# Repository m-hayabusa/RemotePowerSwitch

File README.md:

# M5Stamp C3 を PC のフロントパネルヘッダに繋いで、電源を Wi-Fi 越しに操作するやつ

## 必要なもの

-   基板
-   1 x M5Stamp C3 Mate あるいは M5Stamp C3U Mate
    -   Mate のセットでなく単体の場合は、適当なロープロファイルピンヘッダとピンソケットも用意してください
-   5 x 1608 チップ抵抗 / 100Ω 程度
-   3 x SOT-23 Nch MOSFET / BSS138 など
-   1 x SOD-123 定電流ダイオード or 定電流レギュレータ / 20mA 程度 NSI45020AT1G など
-   1 x L 字ピンヘッダー / 2.54 mm ピッチ 1 列 5 ピン
-   1 x L 字ピンソケット / 2.54 mm ピッチ 2 列 5 ピン

## つくりかた

-   下: GND ベタがないほう
-   表面: 表面実装部品のパターンがある面
-   裏面: LED+/LED-/PWR#/GND/NC の印字がある面

1. 表面に、定電流ダイオードと MOSFET をはんだづけする
2. 表面に、抵抗をはんだづけする。下から 5 つ
3. 裏面に、1x5 のピンヘッダをはんだづけする。LED+/LED-/PWR#/GND/NC の印字が見える方向
4. M5Stamp C3 に付属のピンヘッダを、M5Stamp にはんだづけする
5. 表面に、M5Stamp C3 に付属のピンソケットをはんだづけする。
   あるいは、M5Stamp につけたピンヘッダを直接基板にはんだづけしてもよい
6. 表面に、2x5 のピンソケットをはんだづけする。
   シルクで印がしてあるピンはマザーボード側で欠けてあるピンなので、可能ならソケットからピンを抜いて UV レジンか何かで埋めておくとよい
7. M5Stamp にファームウェアを書きこむ

## ファームウェアの書き込み; 初回

1. VisualStudio Code にプラグイン PlatformIO を追加
2. https://github.com/m-hayabusa/RemotePowerSwitch.git を clone する
3. PlatformIO で 2. のディレクトリを開く。VSCode の左側のバー、なんか触覚が生えてる顔のアイコンから
4. 下のバーの「Default (RemotePowerSwitch)」の部分をクリック、M5Stamp-C3 か M5Stamp-C3U かを選択
5. 下のバーの「→」をクリック、Upload
6. 適当なシリアルモニターで M5Stamp のポートを開く。PlatformIO なら画面下のバーのプラグのアイコンから。挙動が怪しいような気がするので Arduino IDE のシリアルモニタがおすすめ
7. シリアルモニターでこれらを送って設定:

```
WIFI.SSID:(2.4GHz な Wi-Fi ネットワークの SSID)
WIFI.PASSWORD:(Wi-Fi ネットワークのパスワード)
WEB.HOSTNAME:(mDNS で宣伝するホスト名)
WEB.PASSWORD:(Webページから操作するときに必要なパスワード, 設定しなければパスワードなしで操作できます / 解除する場合は空の文字列を設定)
```

8. "http://" + WEB.HOSTNAME + ".local"で接続できるはずです

## ファームウェアの更新

1. PlatformIO でファームウェアをビルド (下のバーの「✔️」)
2. "http://" + WEB.HOSTNAME + ".local/update" をブラウザで開く
3. Firmware.bin のボタンをクリック、プロジェクトのディレクトリ/.pio/M5Stamp-C3/firmware.bin を選択
4. Upload をクリック
5. アップロード・書き込みが終わると自動で再起動します

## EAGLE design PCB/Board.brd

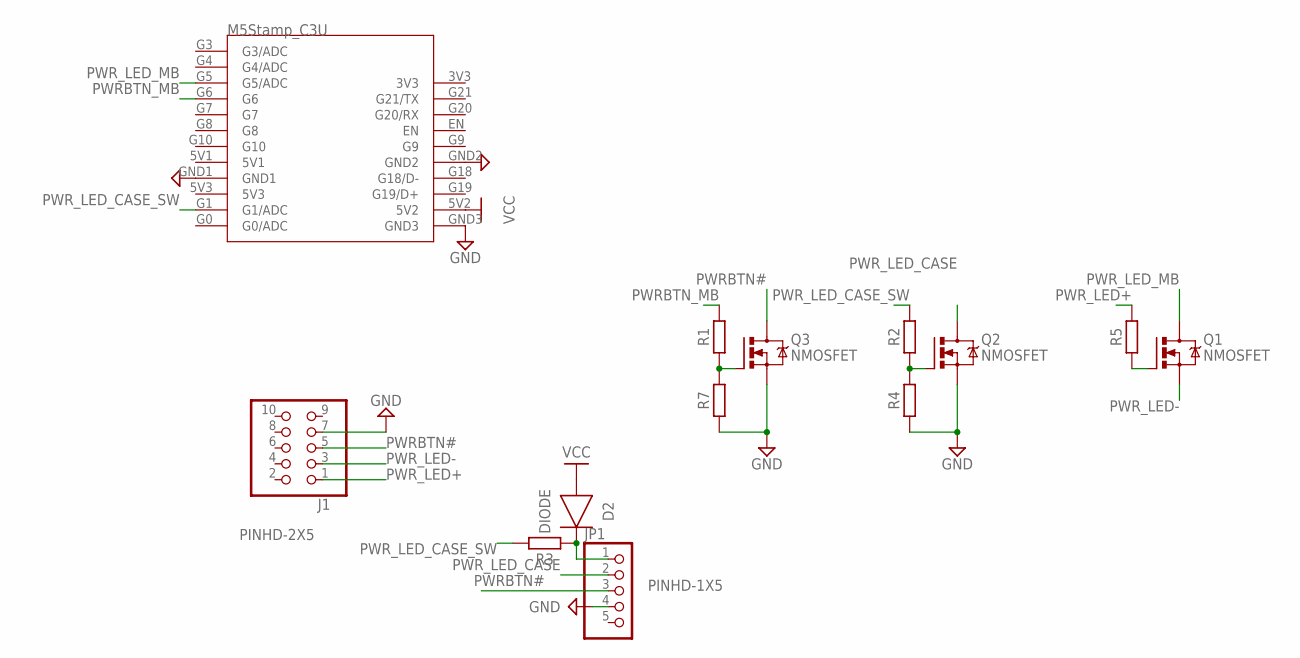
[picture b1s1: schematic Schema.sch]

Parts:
D2: DIODE; SODFL3718X115
J1: PINHD-2X5; 2X05
JP1: PINHD-1X5; 1X05
Q1, Q2, Q3: NMOSFET; SOT23
R1, R2, R3, R4, R5, R7: R_CHIP-0603(1608-METRIC); RESC1608X60
U$1: M5STAMP_C3UHEADER; M5STAMP_C3U_HEADER

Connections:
GND: J1.7, JP1.4, Q2.2 (S), Q3.2 (S), R4.1, R7.1, U$1.GND1, U$1.GND2, U$1.GND3
unnamed: Q3.1 (G), R1.1, R7.2
unnamed: Q2.1 (G), R2.1, R4.2
unnamed: D2.1 (C), JP1.1, R3.1
unnamed: Q1.1 (G), R5.1
PWRBTN#: J1.5, JP1.3, Q3.3 (D)
PWRBTN_MB: R1.2, U$1.G6
PWR_LED+: J1.1, R5.2
PWR_LED-: J1.3, Q1.2 (S)
PWR_LED_CASE: JP1.2, Q2.3 (D)
PWR_LED_CASE_SW: R2.2, R3.2, U$1.G1 (G1/ADC)
PWR_LED_MB: Q1.3 (D), U$1.G5 (G5/ADC)
VCC: D2.2 (A), U$1.5V2

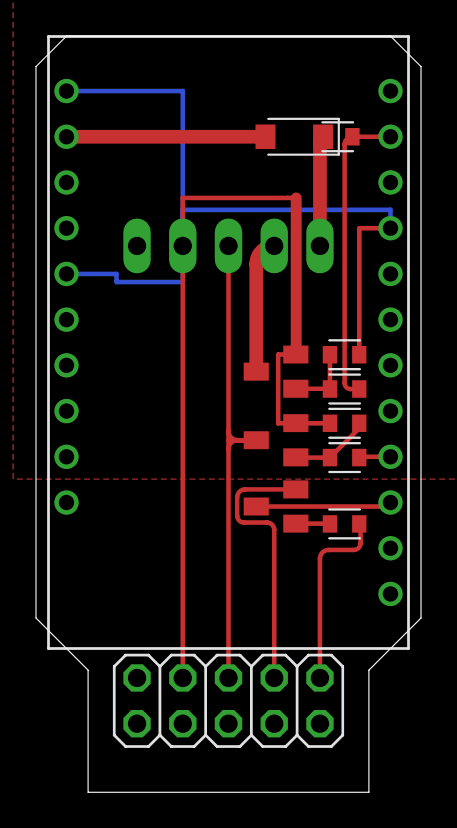
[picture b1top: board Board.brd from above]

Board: 2 copper layers, 21.4 x 42.0 mm, 13 parts (1 on the bottom side), 13 nets.

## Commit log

2023-01-10 Create LICENSE
2023-01-12 C3UでUSBシリアルを使うときの設定
2023-01-12 HTMLファイルの挿入方法を変更
2023-01-12 OTAアップデートできるように
2023-01-12 トップページをいい感じに
2023-01-12 初期化処理をsetupからそれぞれのタスクに移動
2023-01-12 トップページを携帯で見たときいい感じに
2023-01-13 グローバルな変数を減らす
2023-01-17 pinModeの設定ミス
2023-03-30 staticである意味がなかったので外した
2023-03-30 シリアルの受信バッファに何もないとき、待機せずループしていたのを修正
2023-03-30 光り方の違いがそこまでないのでsinを通すのをやめた
2023-03-30 シリアル通信の速度を変更
2023-03-31 パスを相対で指定するように変更
2023-03-31 見た目の調整
2023-03-31 シリアルの読み込み待機を減らした
2023-03-31 タスクの割り当てを変更
2023-04-01 フォーマッタの設定
2023-06-04 再起動できるように
2023-06-04 Wi-Fiから切断されたとき、再接続するように
2023-06-06 Wi-Fiに再接続したとき、IPを取得できないことがあったのを修正
2023-07-12 基板のデータを追加 (Fusion 360 / EasyEDA)
2023-07-30 つくりかたを追記
2023-08-07 CRを無視するように
2023-08-07 PlatformIOのシリアルモニタから正しく設定できるように
2023-08-09 基板を更新: LEDを5Vから駆動するようにしたりRESET / HDDLEDを触らないようにしたり
